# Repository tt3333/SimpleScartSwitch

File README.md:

[日本語版 README はこちら](README-ja.md)

# Simple SCART Switch

This is a switcher that can switch between two SCART inputs.

Cheap SCART switchers sold at AliExpress for less than 1000 Japanese yen only support composite and not RGB.<br>
Most SCART switchers that support RGB have more input terminals than necessary, so they take up a lot of space and are expensive.<br>
Therefore, I designed a simple 2-input switcher that supports RGB.

## How to Build

### Required Parts

- SCART plug 2 pcs
    - https://ja.aliexpress.com/item/1005006514947794.html
- SCART socket 2 pcs
    - https://ja.aliexpress.com/item/1005007196215986.html
- switch (8PDT, 1 Row) 1 pc
    - https://ja.aliexpress.com/item/4000353452952.html
    - https://www.amazon.co.jp/dp/B0D8HYP276
- pan head screw (M3, 6-15mm) 2 pcs
- pan head screw (M3, 8-15mm) 4 pcs
- cushion rubber 4 pcs

### Ordering PCBs

Upload gerber.zip to a board manufacturer's website and order the board.<br>
For JLCPCB, it is recommended to select "Yes" from the "Remove Order Number" options.

### Printing Cases

Print top.stl, bottom.stl and plug_cap.stl with a 3D printer.<br>
If the switch does not come with a cap, please also print switch_cap.stl.

### Assembly

1. Place pieces of paper between the pins of the SCART plugs and the board,<br>
   and temporarily fix the SCART plugs with cellophane tape or similar.
2. Solder the pins on both ends of the SCART plugs.
3. Remove the tape and paper and solder the remaining pins of the SCART plugs.
4. Solder the switch.
5. Solder the SCART sockets.
6. Fasten the board to the case with two screws.
7. Close the case with four screws.
8. Attach cushion rubber to the four corners of the bottom.

## How to Use

- Connect either the left or right plug to the output destination device.<br>
  (Do not use both left and right plugs at the same time.)<br>
  You can align the wiring direction by using the right side plug when connecting to the RetroTINK-5X Pro or the left side plug when connecting to the RetroTINK-4K Pro.
- Put the cap on the plug of the one not in use.
- Connect input sources such as game consoles to the sockets on the top.
- You can switch inputs with the switch on the front.

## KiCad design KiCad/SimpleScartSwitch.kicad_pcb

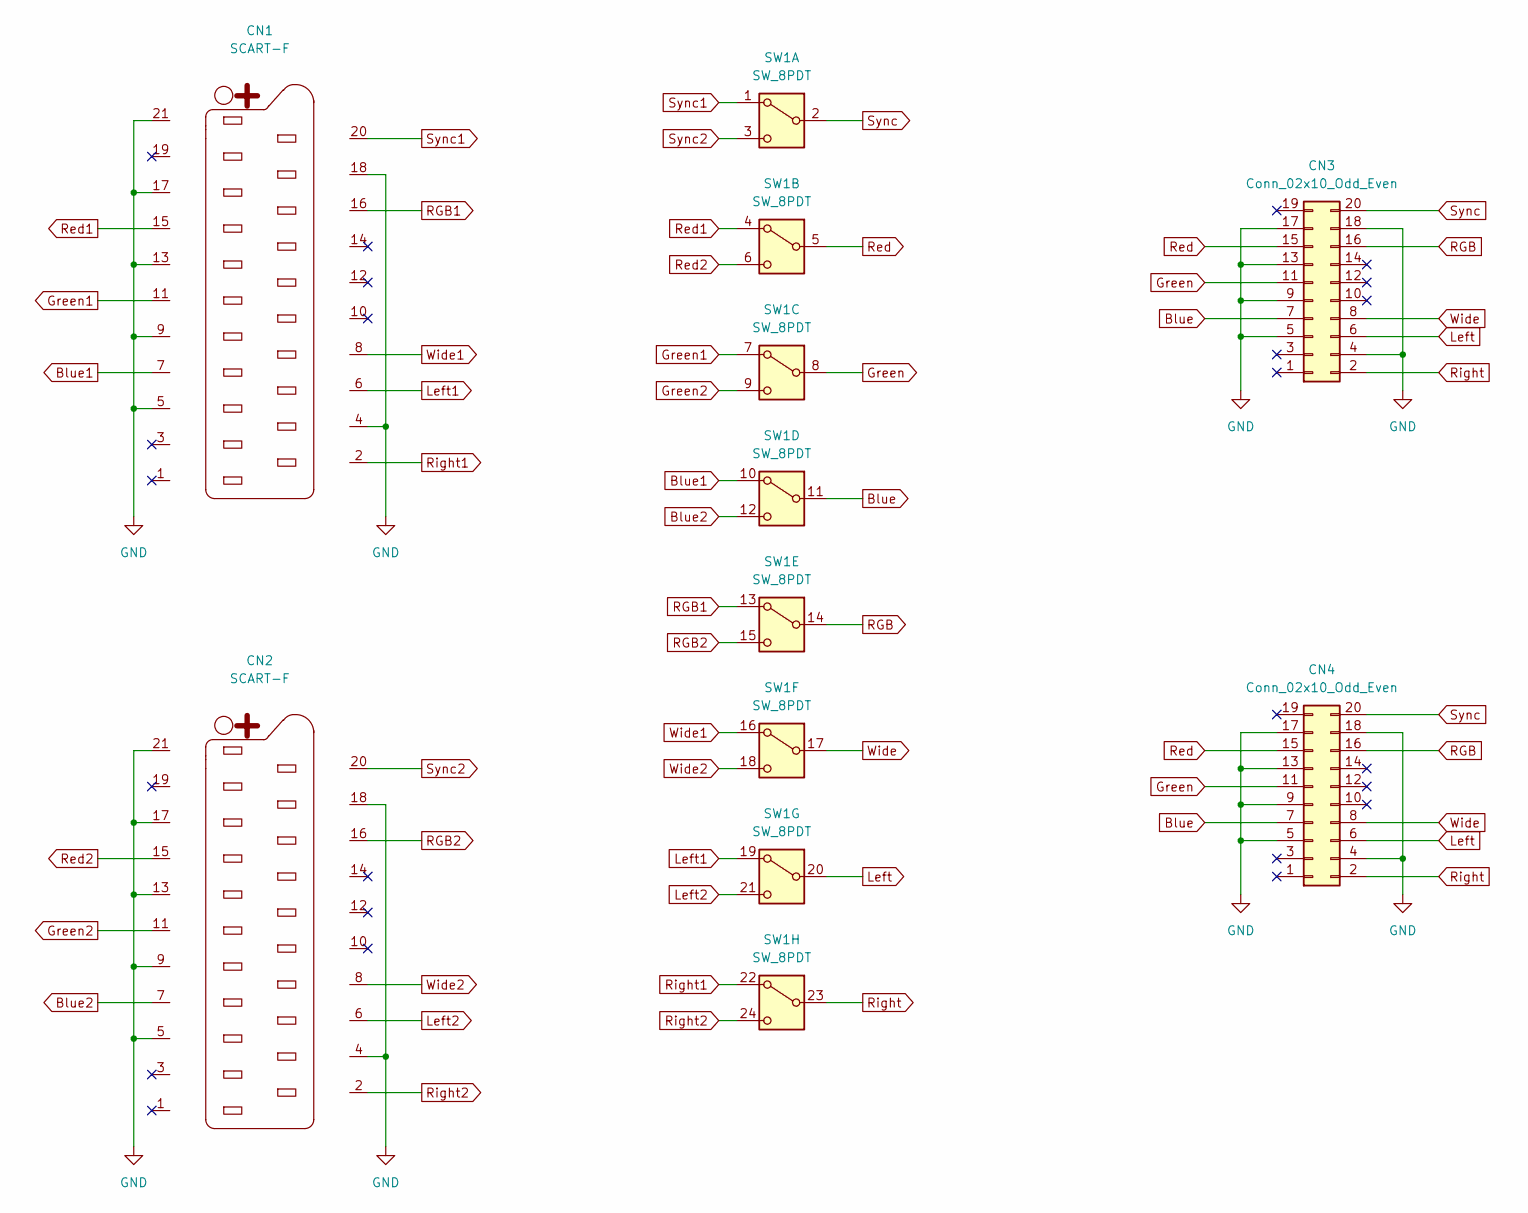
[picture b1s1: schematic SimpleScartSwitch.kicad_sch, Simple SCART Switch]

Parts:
CN1, CN2: SCART-F; SCART_Socket
CN3, CN4: Conn_02x10_Odd_Even; SCART_Plug
SW1: SW_8PDT; 8PDT

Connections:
Blue: CN3.7, CN4.7, SW1.11 (B)
Blue1: CN1.7, SW1.10 (A)
Blue2: CN2.7, SW1.12 (C)
GND: CN1.4, CN1.5, CN1.9, CN1.13, CN1.17, CN1.18, CN1.21, CN2.4, CN2.5, CN2.9, CN2.13, CN2.17, CN2.18, CN2.21, CN3.4, CN3.5, CN3.9, CN3.13, CN3.17, CN3.18, CN4.4, CN4.5, CN4.9, CN4.13, CN4.17, CN4.18
Green: CN3.11, CN4.11, SW1.8 (B)
Green1: CN1.11, SW1.7 (A)
Green2: CN2.11, SW1.9 (C)
Left: CN3.6, CN4.6, SW1.20 (B)
Left1: CN1.6, SW1.19 (A)
Left2: CN2.6, SW1.21 (C)
RGB: CN3.16, CN4.16, SW1.14 (B)
RGB1: CN1.16, SW1.13 (A)
RGB2: CN2.16, SW1.15 (C)
Red: CN3.15, CN4.15, SW1.5 (B)
Red1: CN1.15, SW1.4 (A)
Red2: CN2.15, SW1.6 (C)
Right: CN3.2, CN4.2, SW1.23 (B)
Right1: CN1.2, SW1.22 (A)
Right2: CN2.2, SW1.24 (C)
Sync: CN3.20, CN4.20, SW1.2 (B)
Sync1: CN1.20, SW1.1 (A)
Sync2: CN2.20, SW1.3 (C)
Wide: CN3.8, CN4.8, SW1.17 (B)
Wide1: CN1.8, SW1.16 (A)
Wide2: CN2.8, SW1.18 (C)

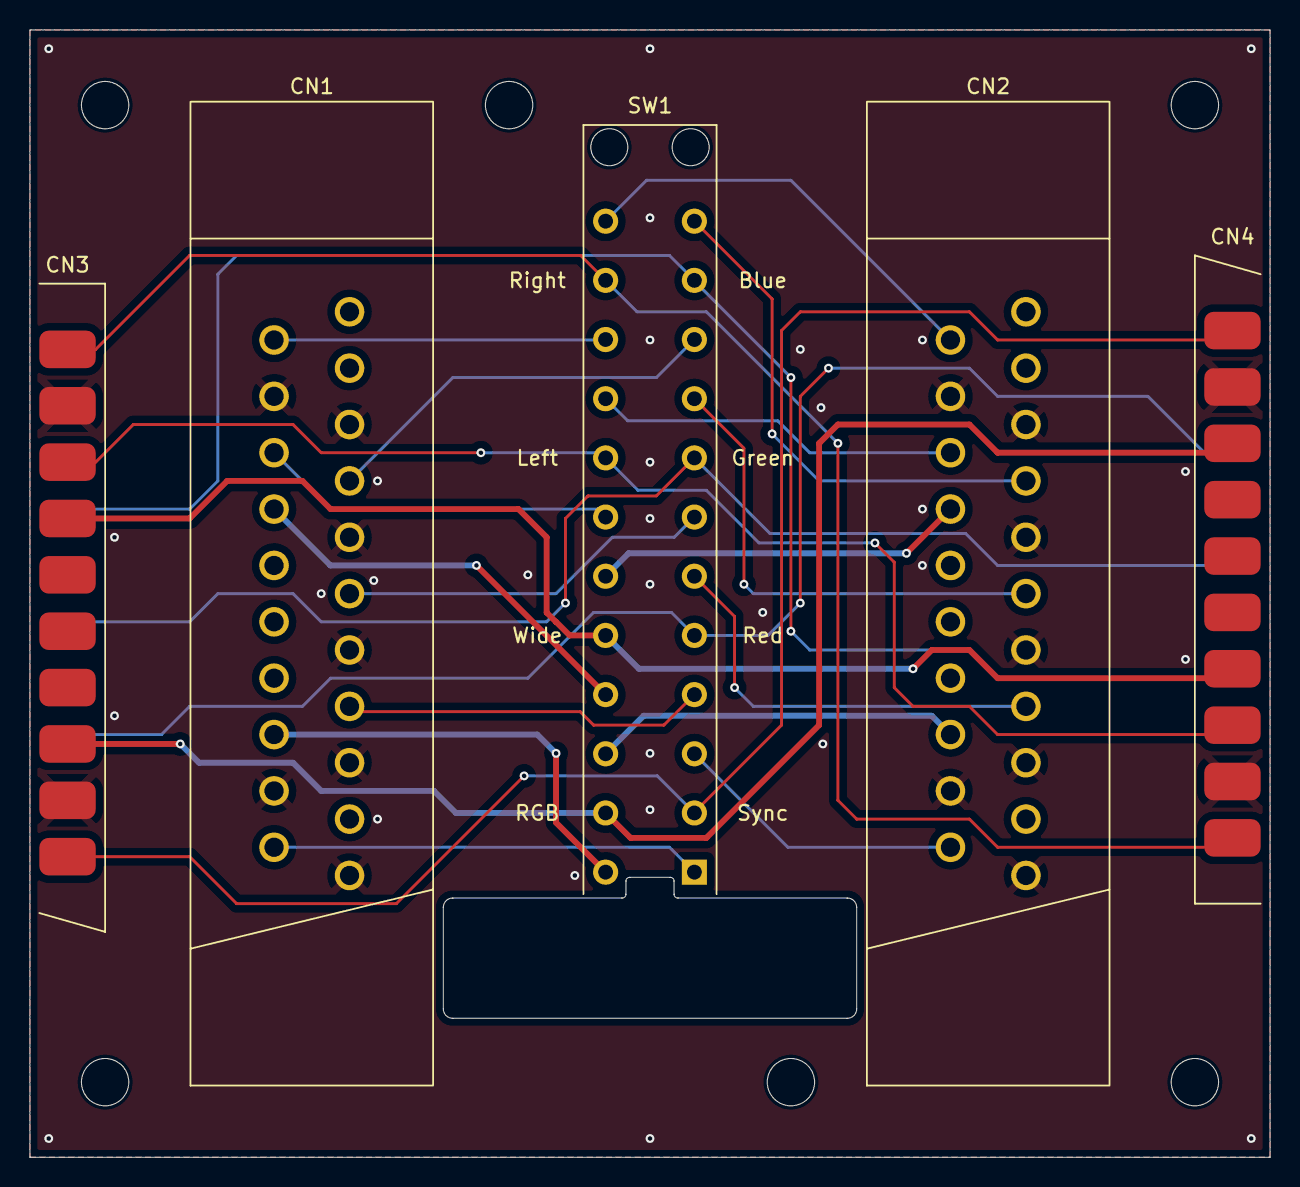
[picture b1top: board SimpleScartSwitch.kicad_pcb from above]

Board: 2 copper layers, 83.8 x 76.2 mm, 5 parts (0 on the bottom side), 25 nets.

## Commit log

2025-01-20 add .gitignore
2025-02-01 add schematic.pdf
2025-02-01 add gerber file
2025-02-01 add PCB image
2025-02-01 add KiCad project
2025-03-26 add FreeCAD project
2025-05-18 SCART plugs can be soldered directly to the board
2025-05-18 add readme

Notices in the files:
KiCad/SimpleScartSwitch.kicad_pcb:
© 2025 T.T
